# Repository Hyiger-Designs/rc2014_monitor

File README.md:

RC2014 compatible Z80 Debug monitor. Design file are for Kicad 5.1+

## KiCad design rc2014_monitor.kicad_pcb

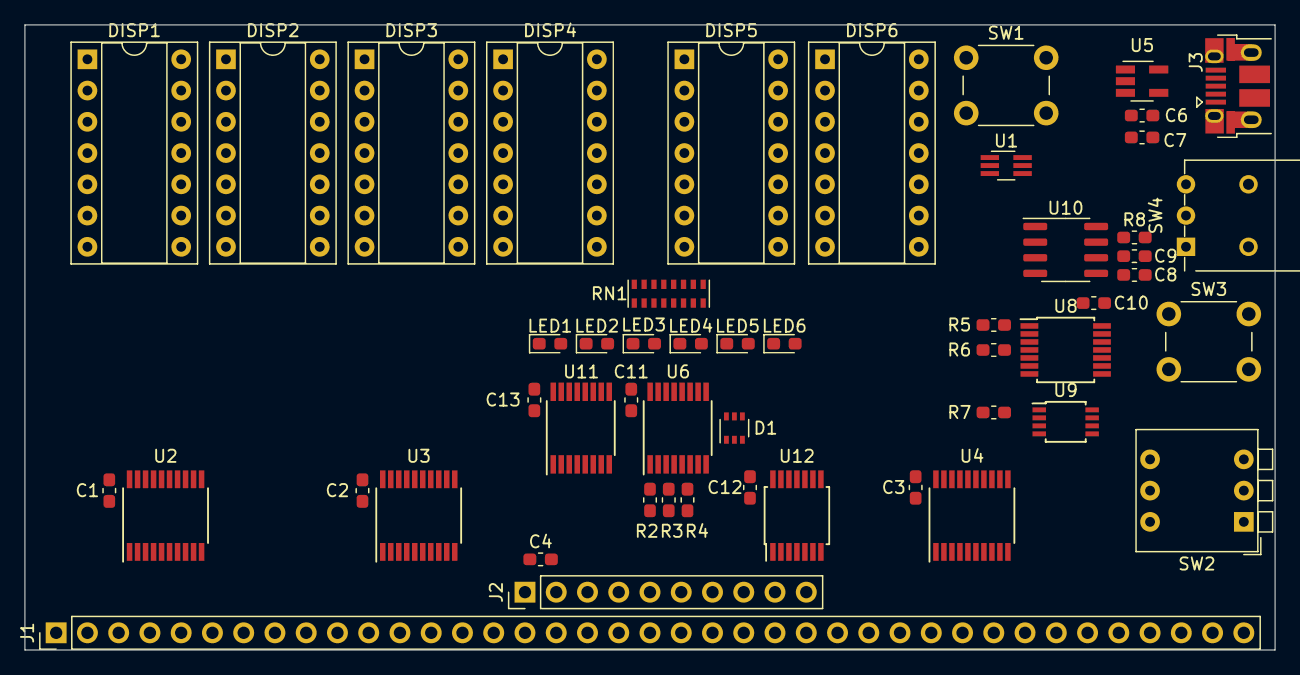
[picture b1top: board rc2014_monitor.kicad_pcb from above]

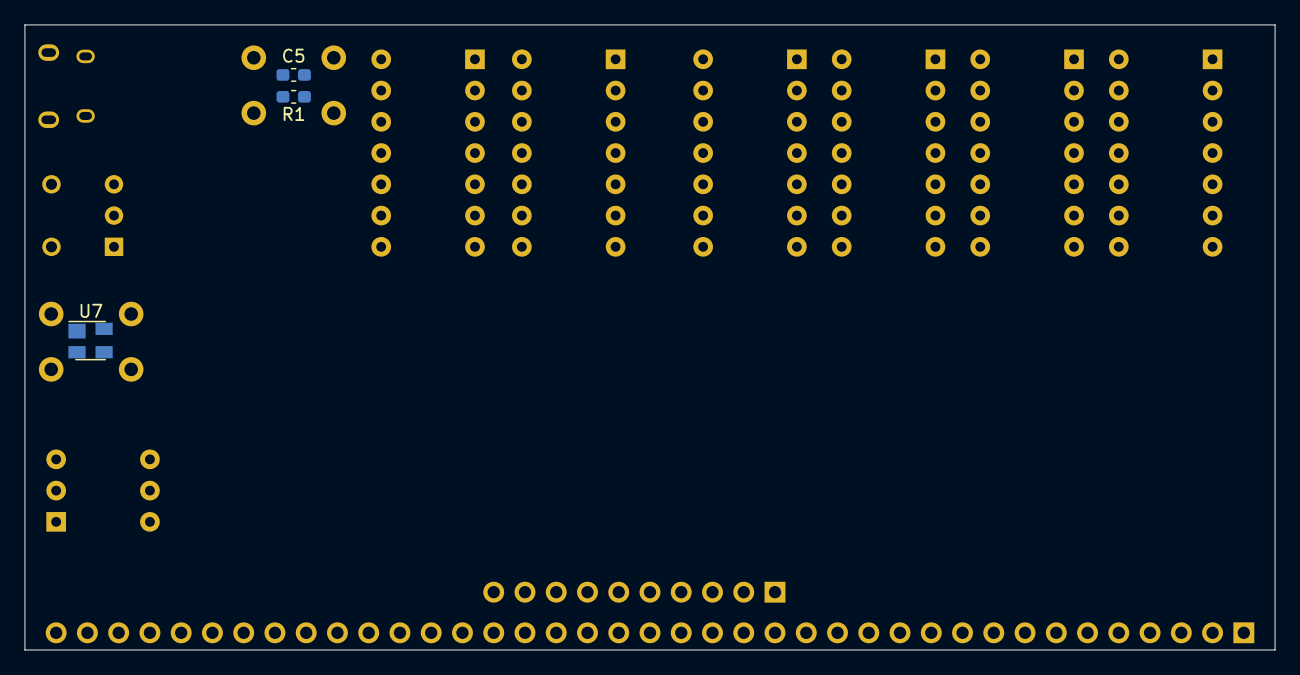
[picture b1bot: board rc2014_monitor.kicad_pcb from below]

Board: 2 copper layers, 101.6 x 50.8 mm, 54 parts (3 on the bottom side), 94 nets, no tracks yet.

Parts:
C1, C2, C3, C4, C6, C10, C11, C12, C13: 100nF; C_0603_1608Metric_Pad1.05x0.95mm_HandSolder
C5: 1nF; C_0603_1608Metric_Pad1.05x0.95mm_HandSolder
C7: 1uF; C_0603_1608Metric_Pad1.05x0.95mm_HandSolder
C8, C9: 10nF; C_0603_1608Metric_Pad1.05x0.95mm_HandSolder
D1: SD103ATW; SOT-363_SC-70-6
DISP1, DISP2, DISP3, DISP4, DISP5, DISP6: TIL311; DIP-14_W7.62mm_Socket
J1: Z80 Bus; PinHeader_1x39_P2.54mm_Vertical
J2: Pro Bus; PinHeader_1x10_P2.54mm_Vertical
J3: USB_B_Micro; USB_Micro-B_Amphenol_10103594-0001LF_Horizontal
LED1, LED2, LED3, LED4, LED5, LED6: SMD Red 620nm 40mcd 2.2V; 20mA; LED_0603_1608Metric_Pad1.05x0.95mm_HandSolder
R1: 1K; R_0603_1608Metric_Pad1.05x0.95mm_HandSolder
R2, R3, R4, R5, R6, R7, R8: 10K; R_0603_1608Metric_Pad1.05x0.95mm_HandSolder
RN1: R_Pack08; R_Cat16-8
SW1, SW3: SW_Push; SW_PUSH_6mm
SW2: SW_DIP_x03; SW_DIP_SPSTx03_Piano_CTS_Series194-3MSTN_W7.62mm_P2.54mm
SW4: Run/Step Mode; SW_NKK_BB15AH
U1: 74LVC2G14; SOT-363_SC-70-6_Handsoldering
U2, U3, U4: 74HCT541PW; TSSOP-20_4.4x6.5mm_P0.65mm
U5: MAX40200AUK; SOT-23-5_HandSoldering
U6: 74HCT138; TSSOP-16_4.4x5mm_P0.65mm
U7: MAX6816; SOT-143
U8: 74HCT74; TSSOP-14_4.4x5mm_P0.65mm
U9: 74HCT2G00; TSSOP-8_3x3mm_P0.65mm
U10: LMC555xN; SOIC-8_3.9x4.9mm_P1.27mm
U11: 74HCT151; TSSOP-16_4.4x5mm_P0.65mm
U12: 74HCT32; TSSOP-14_4.4x5mm_P0.65mm

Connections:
5V: C1.1, C2.1, C3.1, C4.2, C6.1, C7.1, C10.1, C11.1, C12.1, C13.1, DISP1.1, DISP1.14, DISP2.1, DISP2.14, DISP3.1, DISP3.14, DISP4.1, DISP4.14, DISP5.1, DISP5.14, DISP6.1, DISP6.14, J1.18, J2.2, R1.2, R2.2, R3.2, R4.2, R5.1, R6.1, R7.2, R8.2, RN1.9, RN1.10, RN1.11, RN1.12, RN1.13, RN1.14, RN1.15, RN1.16, U2.20, U3.20, U4.20, U5.5, U6.6, U6.16, U7.4, U8.14, U10.8, U11.16, U12.14
/LatchSelector/A: R2.1, SW2.6, U6.1, U11.11
/LatchSelector/B: R3.1, SW2.5, U6.2, U11.10
/LatchSelector/C: R4.1, SW2.4, U6.3, U11.9
A0: J1.16, U3.9
A1: J1.15, U3.8
A2: J1.14, U3.7
A3: J1.13, U3.6
A4: J1.12, U3.5
A5: J1.11, U3.4
A6: J1.10, U3.3
A7: J1.9, U3.2
A8: J1.8, U2.9
A9: J1.7, U2.8
A10: J1.6, U2.7
A11: J1.5, U2.6
A12: J1.4, U2.5
A13: J1.3, U2.4
A14: J1.2, U2.3
A15: J1.1, U2.2
D0: J1.27, U4.2
D1: J1.28, U4.3
D2: J1.29, U4.4
D3: J1.30, U4.5
D4: J1.31, U4.6
D5: J1.32, U4.7
D6: J1.33, U4.8
D7: J1.34, U4.9
D_A0: DISP4.3, U3.11
D_A1: DISP4.2, U3.12
D_A2: DISP4.13, U3.13
D_A3: DISP4.12, U3.14
D_A4: DISP3.3, U3.15
D_A5: DISP3.2, U3.16
D_A6: DISP3.13, U3.17
D_A7: DISP3.12, U3.18
D_A8: DISP2.3, U2.11
D_A9: DISP2.2, U2.12
D_A10: DISP2.13, U2.13
D_A11: DISP2.12, U2.14
D_A12: DISP1.3, U2.15
D_A13: DISP1.2, U2.16
D_A14: DISP1.13, U2.17
D_A15: DISP1.12, U2.18
D_D0: DISP6.3, U4.18
D_D1: DISP6.2, U4.17
D_D2: DISP6.13, U4.16
D_D3: DISP6.12, U4.15
D_D4: DISP5.3, U4.14
D_D5: DISP5.2, U4.13
D_D6: DISP5.13, U4.12
D_D7: DISP5.12, U4.11
GND: C1.2, C2.2, C3.2, C4.1, C5.2, C6.2, C7.2, C8.2, C9.2, C10.2, C11.2, C12.2, C13.2, DISP1.7, DISP2.7, DISP3.7, DISP4.7, DISP5.7, DISP6.7, J1.17, J2.1, J3.5, J3.6, SW1.2, SW2.1, SW2.2, SW2.3, SW3.1, SW4.2, U1.2, U2.10, U2.19, U3.10, U3.19, U4.10, U4.19, U5.2, U6.4, U6.8, U7.1, U8.7, U8.10, U8.11, U8.12, U8.13, U9.4, U10.1, U11.8, U11.12, U11.13, U11.14, U12.7
IO_RD: U11.4, U12.8
IO_WR: U11.3, U12.11
LATCH: DISP1.5, DISP2.5, DISP3.5, DISP4.5, DISP5.5, DISP6.5, U11.5
M_RD: U11.2, U12.6
M_WR: U11.1, U12.3
unnamed: C5.1, R1.1, SW1.1, U1.1
unnamed: C8.1, U10.5
unnamed: C9.1, R8.1, U10.6, U10.7
unnamed: D1.1, U6.10
unnamed: D1.2, U6.9
unnamed: D1.3, U6.7
unnamed: D1.4, D1.5, D1.6, LED6.1
unnamed: J3.1, U5.1, U5.3
unnamed: LED1.1, U6.15
unnamed: LED1.2, RN1.1
unnamed: LED2.1, U6.14
unnamed: LED2.2, RN1.2
unnamed: LED3.1, U6.13
unnamed: LED3.2, RN1.3
unnamed: LED4.1, U6.12
unnamed: LED4.2, RN1.4
unnamed: LED5.1, U6.11
unnamed: LED5.2, RN1.5
unnamed: LED6.2, RN1.6
unnamed: R5.2, U8.2
unnamed: R6.2, U8.4
unnamed: R7.1, SW4.1, U9.2
unnamed: SW3.2, U7.2
unnamed: U7.3, U8.3
unnamed: U8.1, U9.3
unnamed: U8.6, U9.1
unnamed: U9.5, U9.6, U10.3
RST: DISP1.8, DISP2.8, DISP3.8, DISP4.8, DISP5.8, DISP6.8, U1.3, U1.6, U2.1, U3.1, U4.1, U6.5, U11.7
VCC: U1.5, U9.8
~IORQ: J1.26, U12.9, U12.13
~M1: J1.19, U10.2, U10.4, U11.15
~MREQ: J1.23, U12.2, U12.4
~RD: J1.25, U12.5, U12.10
~RST: J1.20, U1.4
~WAIT: J2.9, U9.7
~WR: J1.24, U12.1, U12.12

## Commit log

2019-04-04 initial version
2019-04-05 started adding traces
2019-04-05 finished traces and silkscreens
2019-04-06 updated boms
2019-04-08 more appropriate latch options
2019-04-08 Added io_rd/wr,mem_rd/wr for latch options
2019-04-08 fixed broken traces
2019-04-09 reorganized wiring
2019-04-09 track cleanup
2019-04-10 replaces schottky with ideal diodes
2019-04-11 added additional LED for 5V signal
2019-04-11 Added mounting hole
2019-04-11 moved latch circuit to new sheet
2019-04-11 added diode-AND to unused latch select pins
2019-04-11 added pro bus, generated gerbers
2019-04-13 Added reset circuit
2019-04-13 label updates
2019-04-16 Changed display buffer and other parts
2019-04-16 added single stepping, changed routing and placement
2019-04-17 more routing
2019-04-17 cleaned up routing and layout
2019-04-17 labelling and layout fixes
2019-04-18 changed trace sizes to smaller values
2019-04-18 trace cleanup
2019-04-18 removed some vias
2019-04-18 generated gerbers
2019-04-18 fixed some alignments
2019-04-18 more fixes
2019-04-19 use reset to clear the displays
2019-04-19 Fixed some courtyard overlaps and rotary switch orientation
2019-04-22 changes to stepper circuit, pcb layout changes
2019-04-23 new layout
2019-04-24 added vias for thermal releaf
2019-04-26 cleanup temporary files
2019-04-26 fixed single step, display hookup
2019-04-29 Reorganized board yet again, replaced SMD 555 with TH
2019-04-29 more routing changes
2019-04-30 DRC fixed
2019-04-30 replaced diode array with thru-hole
2019-04-30 cleanup
2019-05-03 added extra filter cap, opened groundplane
2019-05-03 Internalize reset
2019-05-03 extra pins
2019-05-05 schematic cleanup, improved gnd plane
2019-05-06 Swapped out reset, reorganized gnd planes
2019-05-07 fixed up up footprint and traces
2019-05-10 fixed ideal diode caps
2019-05-11 added additional caps
2019-05-12 organized annotations
2019-05-13 removed rotary switch and reset circuit
2019-05-18 fixed traces
2019-08-01 removed rotary, rerouted
2019-08-01 added dip sw for latch selection
2019-08-01 tightened up gnd plane and schematics
2019-08-02 extended active high reset to displays and ics
2019-08-06 fixed via sizes and silk
2019-10-17 SMD version
